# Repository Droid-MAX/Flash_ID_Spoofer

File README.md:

# Flash ID Spoofer

Flash ID Spoofer is a spoof flash id with the help of the EPM3032ATC44-10 (CPLD) chip.

**License**

This is free software: you can redistribute it and/or modify it under the terms of
the latest GNU General Public License as published by the Free Software Foundation.

This program is distributed in the hope that it will be useful, but WITHOUT ANY WARRANTY;
without even the implied warranty of MERCHANTABILITY or FITNESS FOR A PARTICULAR PURPOSE.
See the GNU General Public License for more details.

You should have received a copy of the GNU General Public License along with this program.
If not, see <http://www.gnu.org/licenses/>.

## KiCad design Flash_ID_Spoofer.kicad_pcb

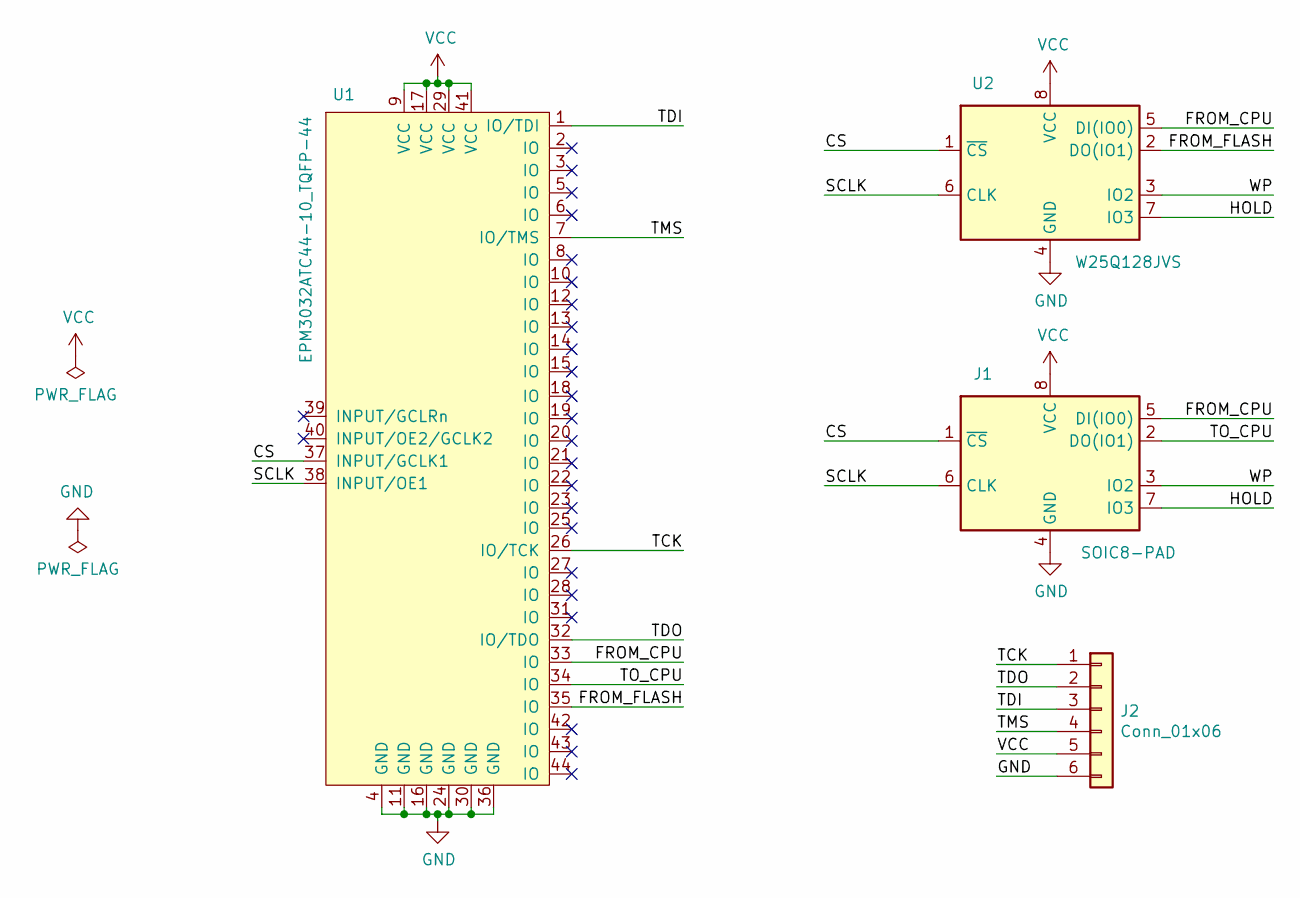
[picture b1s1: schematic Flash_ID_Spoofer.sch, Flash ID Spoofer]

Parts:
J1: SOIC8-PAD; SOIC-8-PAD_5.23x5.23mm_P1.27mm
J2: Conn_01x06; PinHeader_1x06_P2.00mm_Vertical
U1: EPM3032ATC44-10_TQFP-44; TQFP-44_10x10mm_P0.8mm
U2: W25Q128JVS; SOIC-8_5.23x5.23mm_P1.27mm

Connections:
/CS: J1.1 (~CS), U1.37 (INPUT/GCLK1), U2.1 (~CS)
/FROM_CPU: J1.5 (DI(IO0)), U1.33 (IO), U2.5 (DI(IO0))
/FROM_FLASH: U1.35 (IO), U2.2 (DO(IO1))
/HOLD: J1.7 (IO3), U2.7 (IO3)
/SCLK: J1.6 (CLK), U1.38 (INPUT/OE1), U2.6 (CLK)
/TCK: J2.1, U1.26 (IO/TCK)
/TDI: J2.3, U1.1 (IO/TDI)
/TDO: J2.2, U1.32 (IO/TDO)
/TMS: J2.4, U1.7 (IO/TMS)
/TO_CPU: J1.2 (DO(IO1)), U1.34 (IO)
/WP: J1.3 (IO2), U2.3 (IO2)
GND: J1.4 (GND), J2.6, U1.4 (GND), U1.11 (GND), U1.16 (GND), U1.24 (GND), U1.30 (GND), U1.36 (GND), U2.4 (GND)
VCC: J1.8 (VCC), J2.5, U1.9 (VCC), U1.17 (VCC), U1.29 (VCC), U1.41 (VCC), U2.8 (VCC)

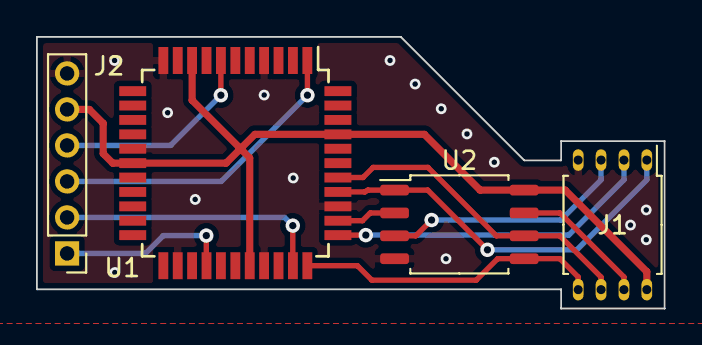
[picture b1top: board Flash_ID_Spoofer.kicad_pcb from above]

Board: 2 copper layers, 34.9 x 15.1 mm, 4 parts (0 on the bottom side), 13 nets.

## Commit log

2021-03-07 first init
2021-03-08 fix detail issues
2021-03-08 adjust details
2021-03-08 Update for PCB
2021-03-08 Update PCB
2021-03-08 add gnd via holes
2021-03-12 Add more GND via holes
2021-03-14 uniform gnd net line to 0.4mm
